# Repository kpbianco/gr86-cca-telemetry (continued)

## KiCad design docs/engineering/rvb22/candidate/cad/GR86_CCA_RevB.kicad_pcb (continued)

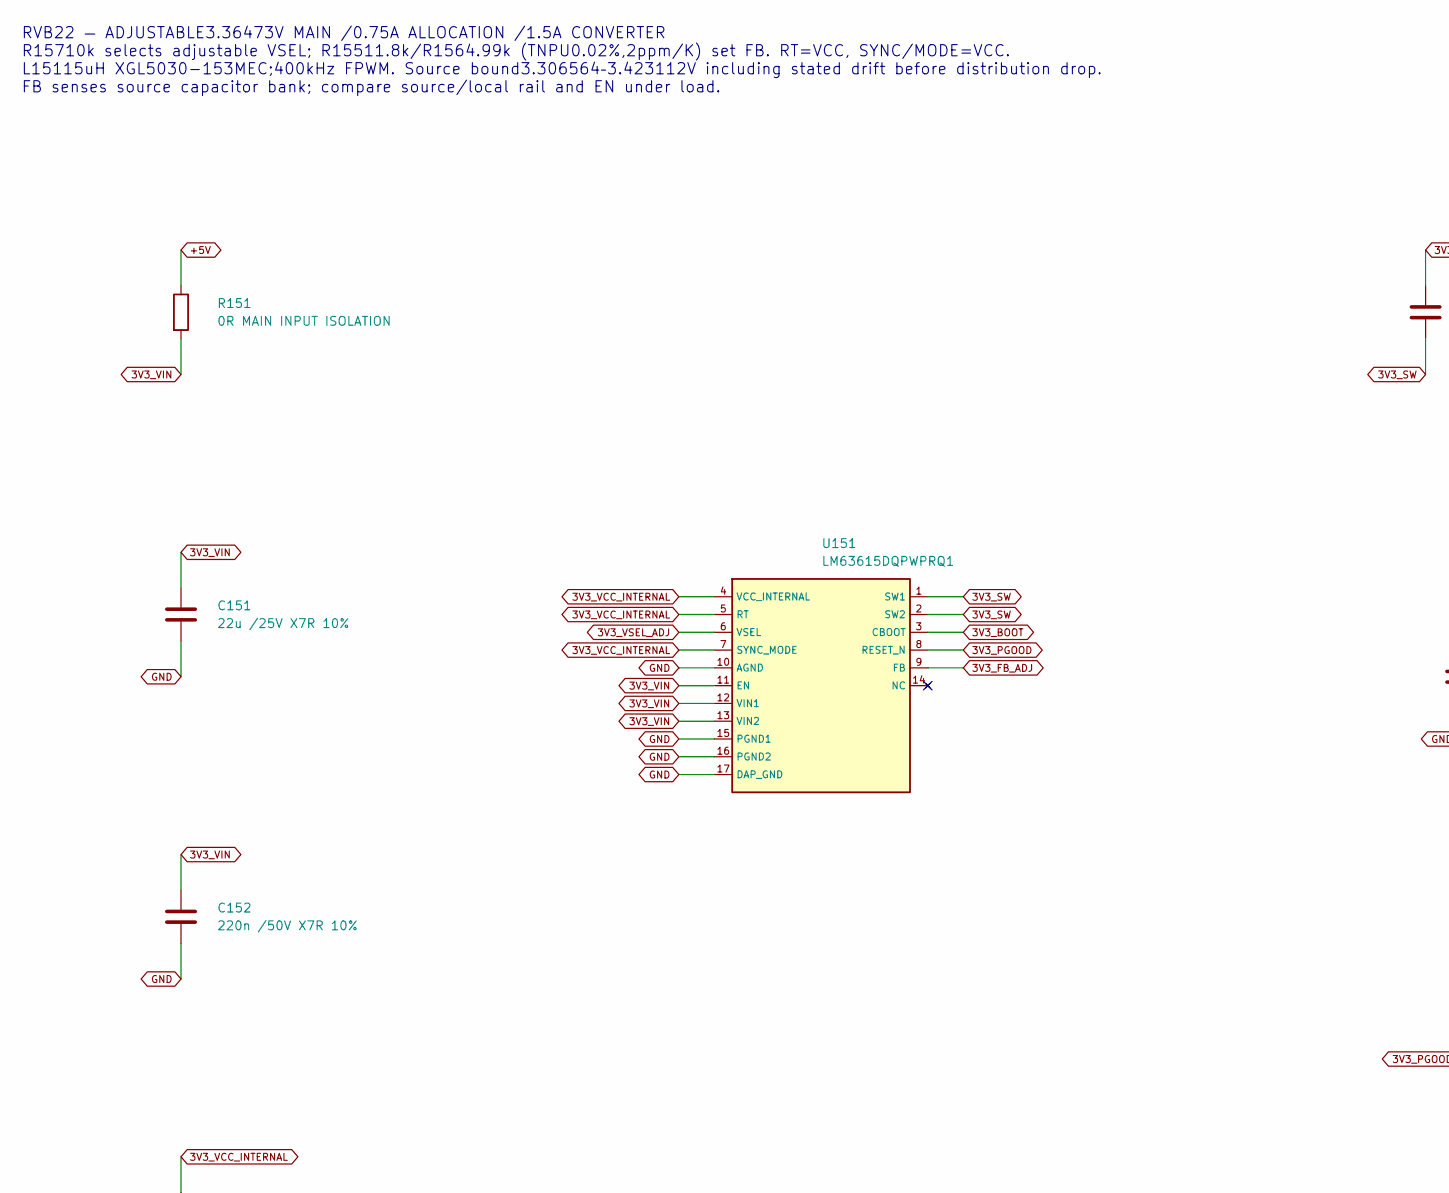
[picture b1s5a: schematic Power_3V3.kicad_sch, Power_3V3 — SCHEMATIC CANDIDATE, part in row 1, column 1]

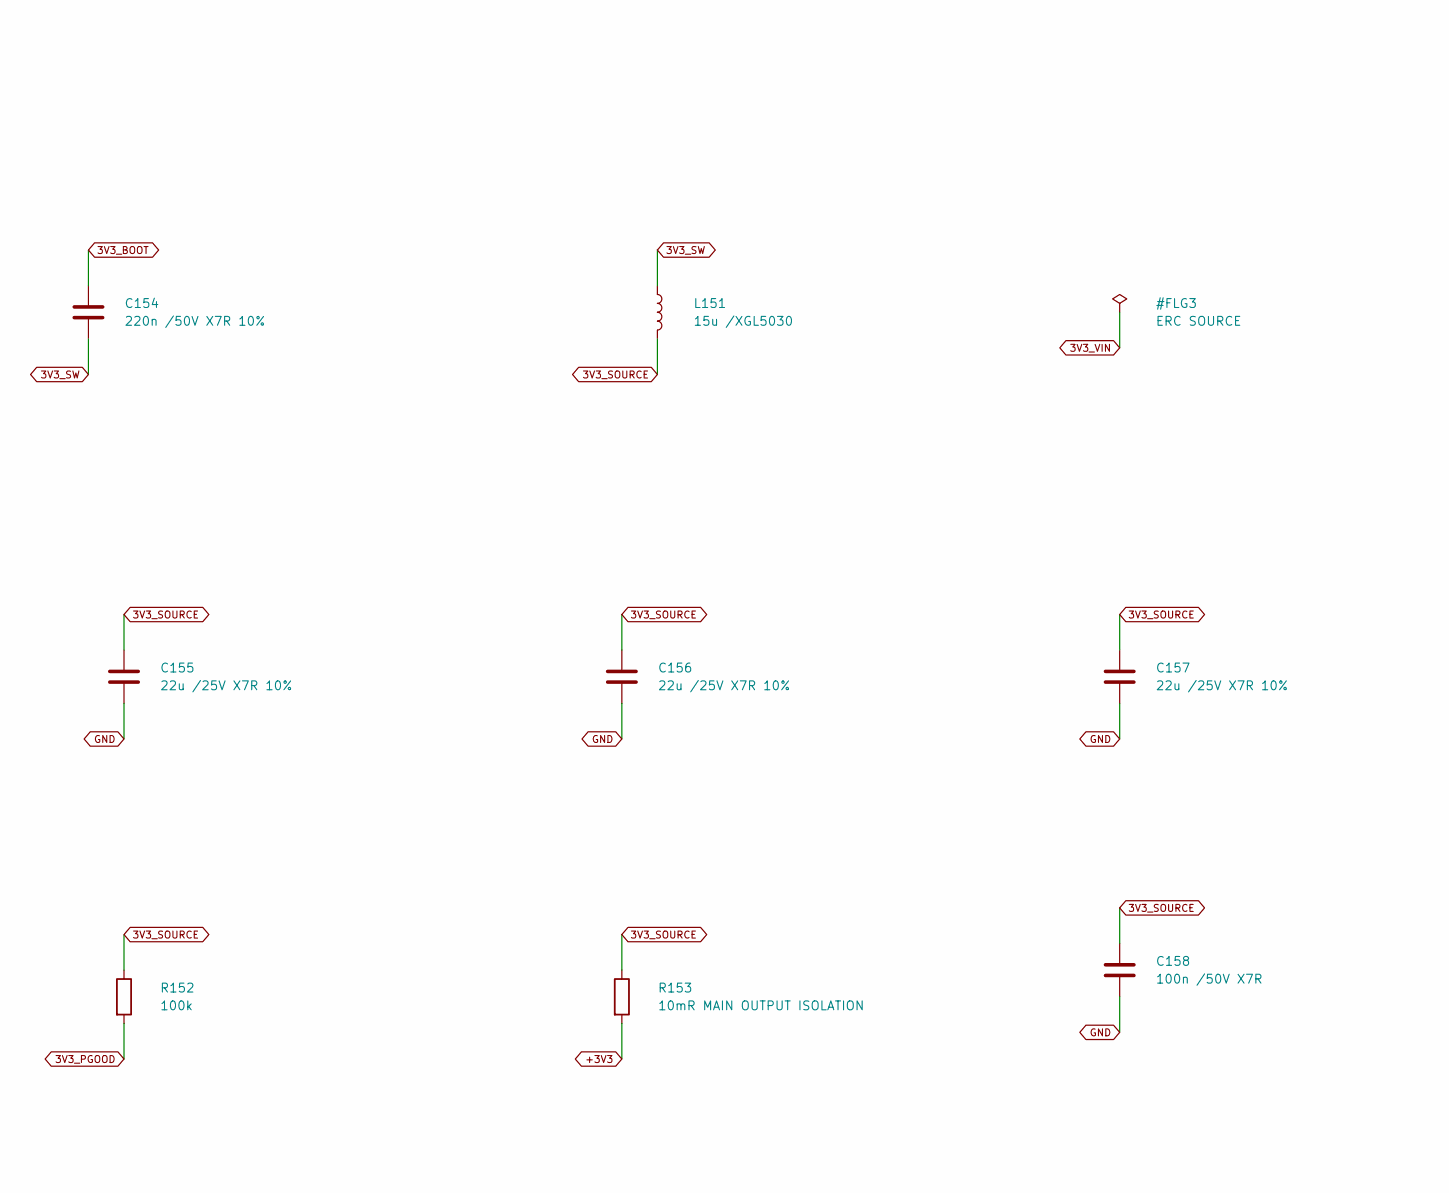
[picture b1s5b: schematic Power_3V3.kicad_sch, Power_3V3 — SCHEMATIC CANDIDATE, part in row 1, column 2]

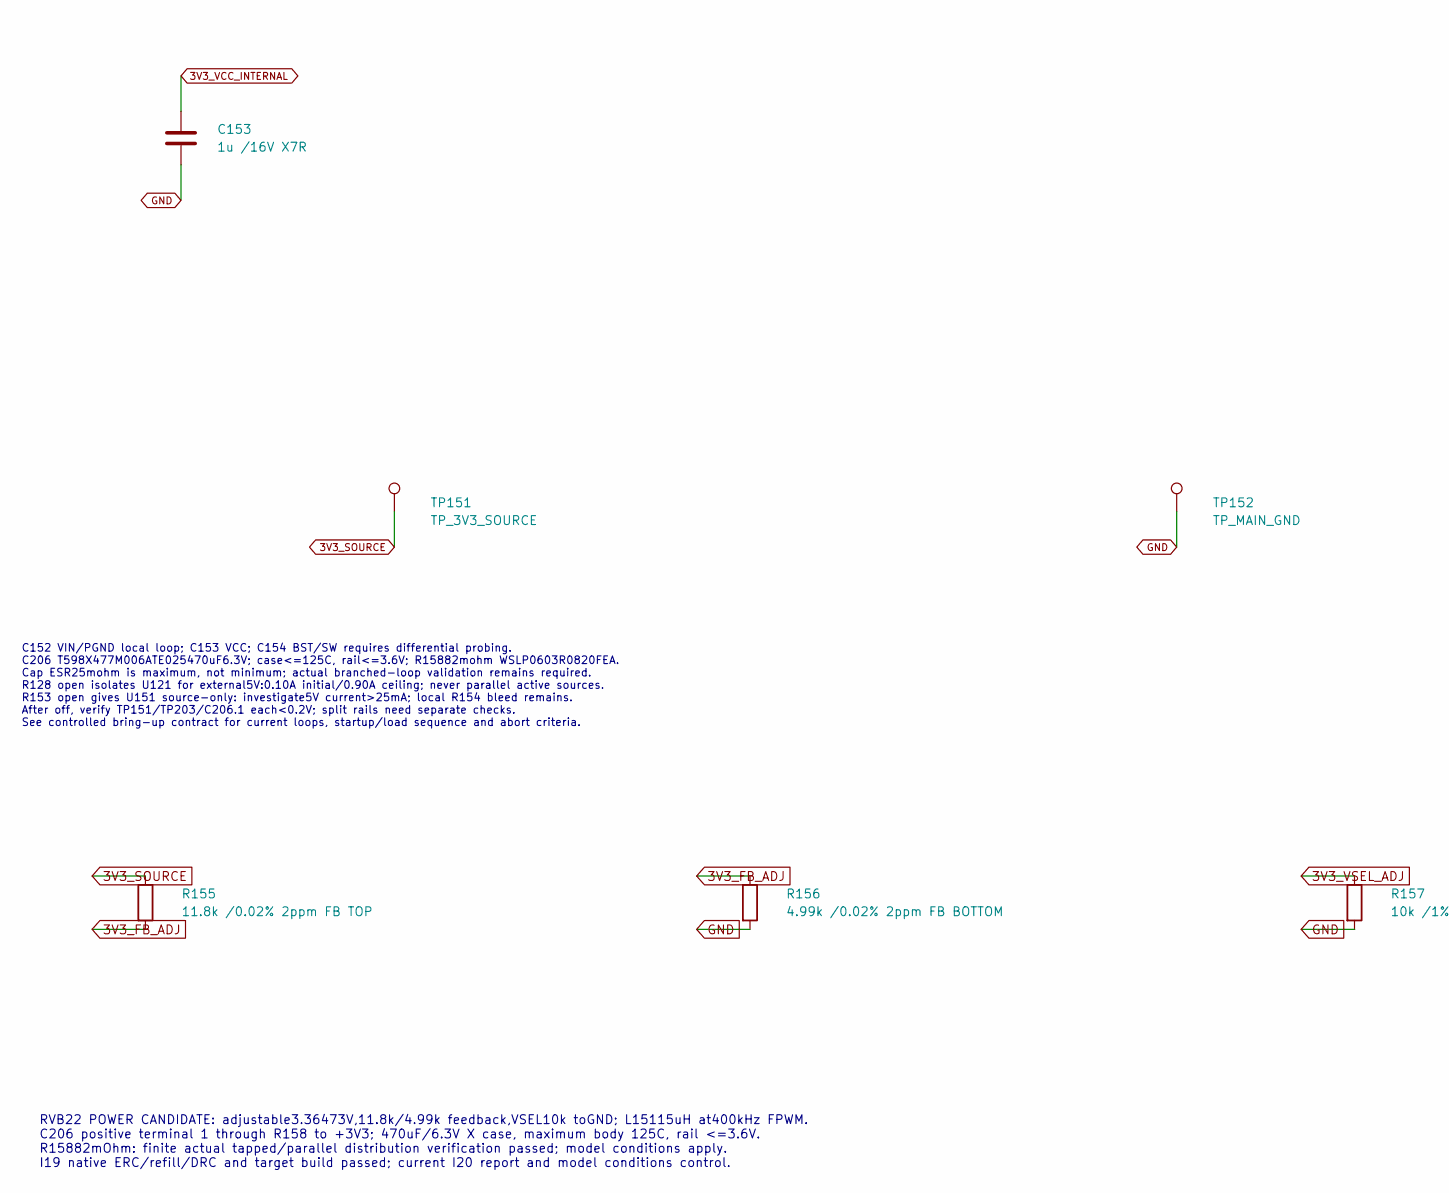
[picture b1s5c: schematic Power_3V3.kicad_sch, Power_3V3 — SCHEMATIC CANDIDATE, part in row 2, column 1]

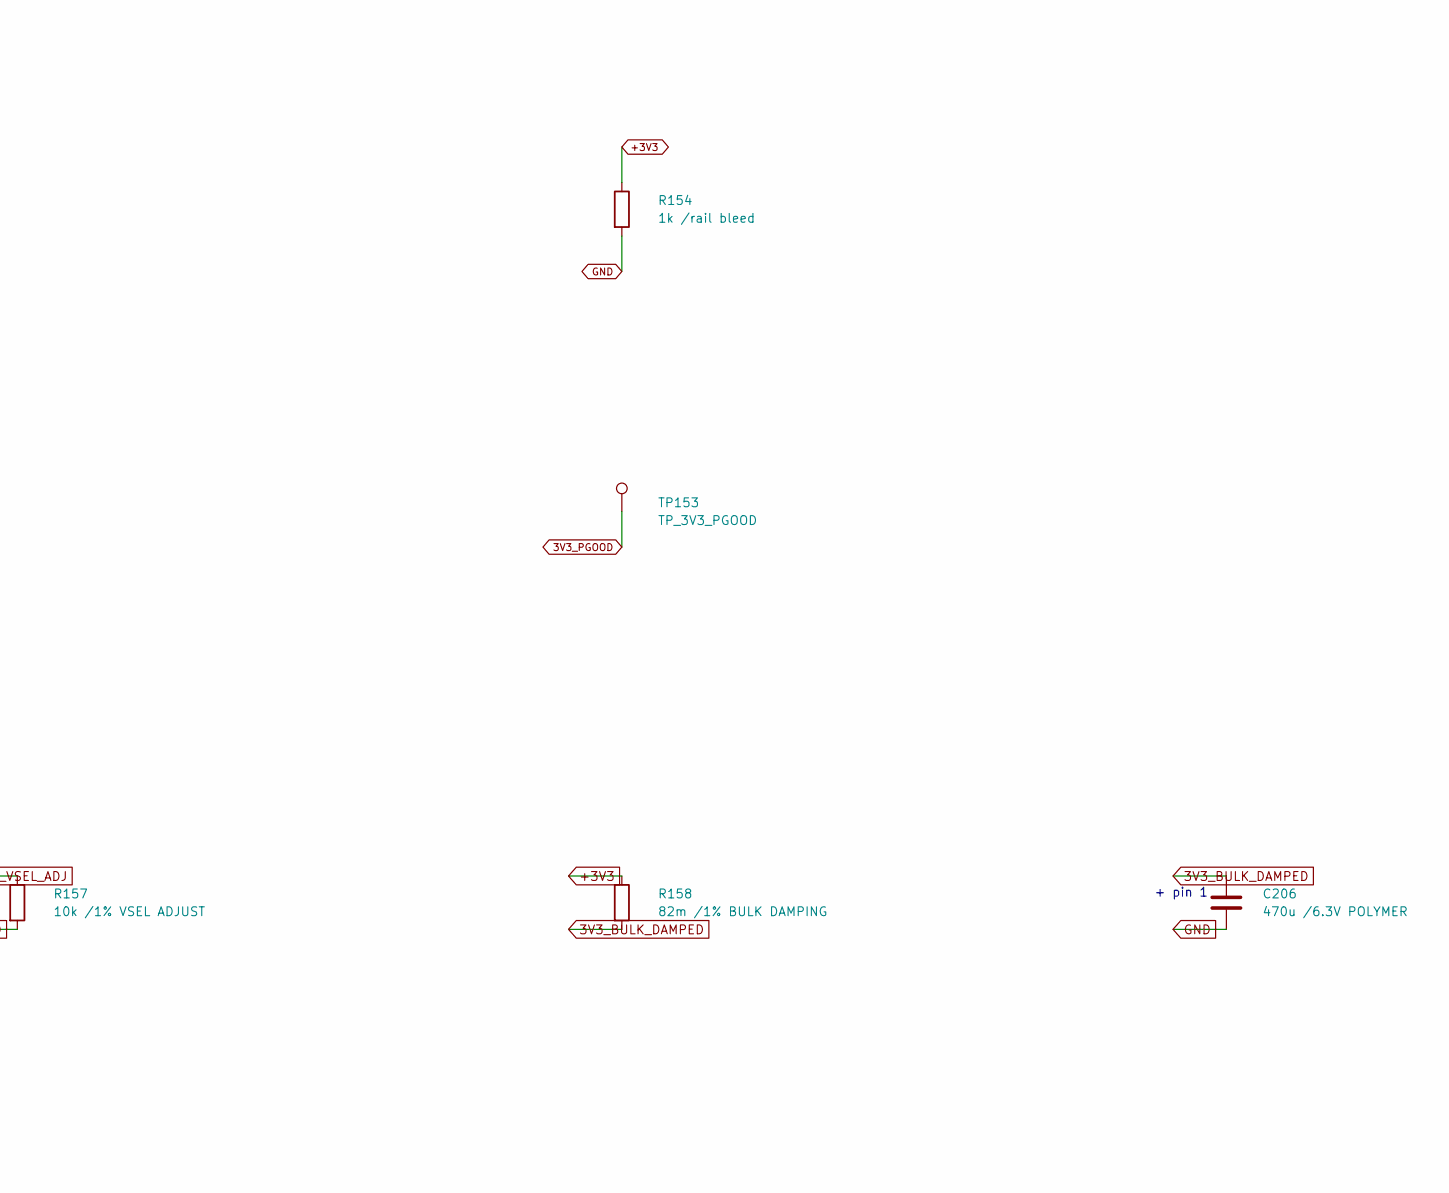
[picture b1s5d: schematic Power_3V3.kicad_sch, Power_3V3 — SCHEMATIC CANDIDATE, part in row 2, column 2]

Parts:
C151, C155, C156, C157: 22u /25V X7R 10%; C_1210_3225Metric; MPN MCAST32MSB7226KPNA01; LCSC C5372271
C152: 220n /50V X7R 10%; C_0603_1608Metric; MPN CGA3E3X7R1H224K080AB; LCSC C342967
C153: 1u /16V X7R; C_0603_1608Metric; MPN GCM188R71C105KA64D; LCSC C161212
C154: 220n /50V X7R 10%; C_0603_1608Metric_RVB22_C154; MPN CGA3E3X7R1H224K080AB; LCSC C342967
C158: 100n /50V X7R; C_0603_1608Metric; MPN GCM188R71H104KA57D; LCSC C85864
C206: 470u /6.3V POLYMER; KEMET_T598_X_7343_Median_RVB22_C206; MPN T598X477M006ATE025
L151: 15u /XGL5030; L_Coilcraft_XAL5030-XXX; MPN XGL5030-153MEC
R151: 0R MAIN INPUT ISOLATION; R_1206_3216Metric; MPN CRCW12060000Z0EA; LCSC C190124
R152: 100k; R_0603_1608Metric; MPN CRCW0603100KFKEA; LCSC C844916
R153: 10mR MAIN OUTPUT ISOLATION; WSLP0603_MANUFACTURER_R153; MPN WSLP0603R0100FEA
R154: 1k /rail bleed; R_0603_1608Metric; MPN CRCW06031K00FKEA; LCSC C844920
R155: 11.8k /0.02% 2ppm FB TOP; R_0603_1608Metric_RVB22_R155; MPN TNPU060311K8HWEA00
R156: 4.99k /0.02% 2ppm FB BOTTOM; R_0603_1608Metric_RVB22_R156; MPN TNPU06034K99HWEA00
R157: 10k /1% VSEL ADJUST; R_0603_1608Metric_RVB22_R157; MPN CRCW060310K0FKEA
R158: 82m /1% BULK DAMPING; WSLP0603_MANUFACTURER; MPN WSLP0603R0820FEA
TP151: TP_3V3_SOURCE; TestPoint_Pad_D1.5mm; MPN BARE PCB PAD
TP152: TP_MAIN_GND; TestPoint_Pad_D1.5mm; MPN BARE PCB PAD
TP153: TP_3V3_PGOOD; TestPoint_Pad_D1.5mm; MPN BARE PCB PAD
U151: LM63615DQPWPRQ1; HTSSOP-16-1EP_4.4x5mm_P0.65mm_EP3.4x5mm_Mask2.46x2.31mm_RVB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; MPN LM63615DQPWPRQ1; LCSC C2867799

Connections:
3V3_BOOT: C154.1, U151.3 (CBOOT)
3V3_BULK_DAMPED: C206.1, R158.2
3V3_FB_ADJ: R155.2, R156.1, U151.9 (FB)
3V3_PGOOD: R152.2, TP153.1, U151.8 (RESET_N)
3V3_SOURCE: C155.1, C156.1, C157.1, C158.1, L151.2, R152.1, R153.1, R155.1, TP151.1
3V3_SW: C154.2, L151.1, U151.1 (SW1), U151.2 (SW2)
3V3_VCC_INTERNAL: C153.1, U151.4 (VCC_INTERNAL), U151.5 (RT), U151.7 (SYNC_MODE)
3V3_VIN: C151.1, C152.1, R151.2, U151.11 (EN), U151.12 (VIN1), U151.13 (VIN2)
3V3_VSEL_ADJ: R157.1, U151.6 (VSEL)
+3V3: R153.2, R154.1, R158.1; also elsewhere on the board
+5V: R151.1; also elsewhere on the board
GND: C151.2, C152.2, C153.2, C155.2, C156.2, C157.2, C158.2, C206.2, R154.2, R156.2, R157.2, TP152.1, U151.10 (AGND), U151.15 (PGND1), U151.16 (PGND2), U151.17 (DAP_GND); also elsewhere on the board

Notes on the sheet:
RVB22 — ADJUSTABLE3.36473V MAIN /0.75A ALLOCATION /1.5A CONVERTER R15710k selects adjustable VSEL; R15511.8k/R1564.99k (TNPU0.02%,2ppm/K) set FB. RT=VCC, SYNC/MODE=VCC. L15115uH XGL5030-153MEC;400kHz FPWM. Source bound3.306564–3.423112V including stated drift before distribution drop. FB senses sou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
C152 VIN/PGND local loop; C153 VCC; C154 BST/SW requires differential probing. C206 T598X477M006ATE025470uF6.3V; case<=125C, rail<=3.6V; R15882mohm WSLP0603R0820FEA. Cap ESR25mohm is maximum, not minimum; actual branched-loop validation remains required. R128 open isolates U121 for external5V:0.10A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
+ pin 1
RVB22 POWER CANDIDATE: adjustable3.36473V,11.8k/4.99k feedback,VSEL10k toGND; L15115uH at400kHz FPWM. C206 positive terminal 1 through R158 to +3V3; 470uF/6.3V X case, maximum body 125C, rail <=3.6V. R15882mOhm: finite actual tapped/parallel distribution verification passed; model conditions apply.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

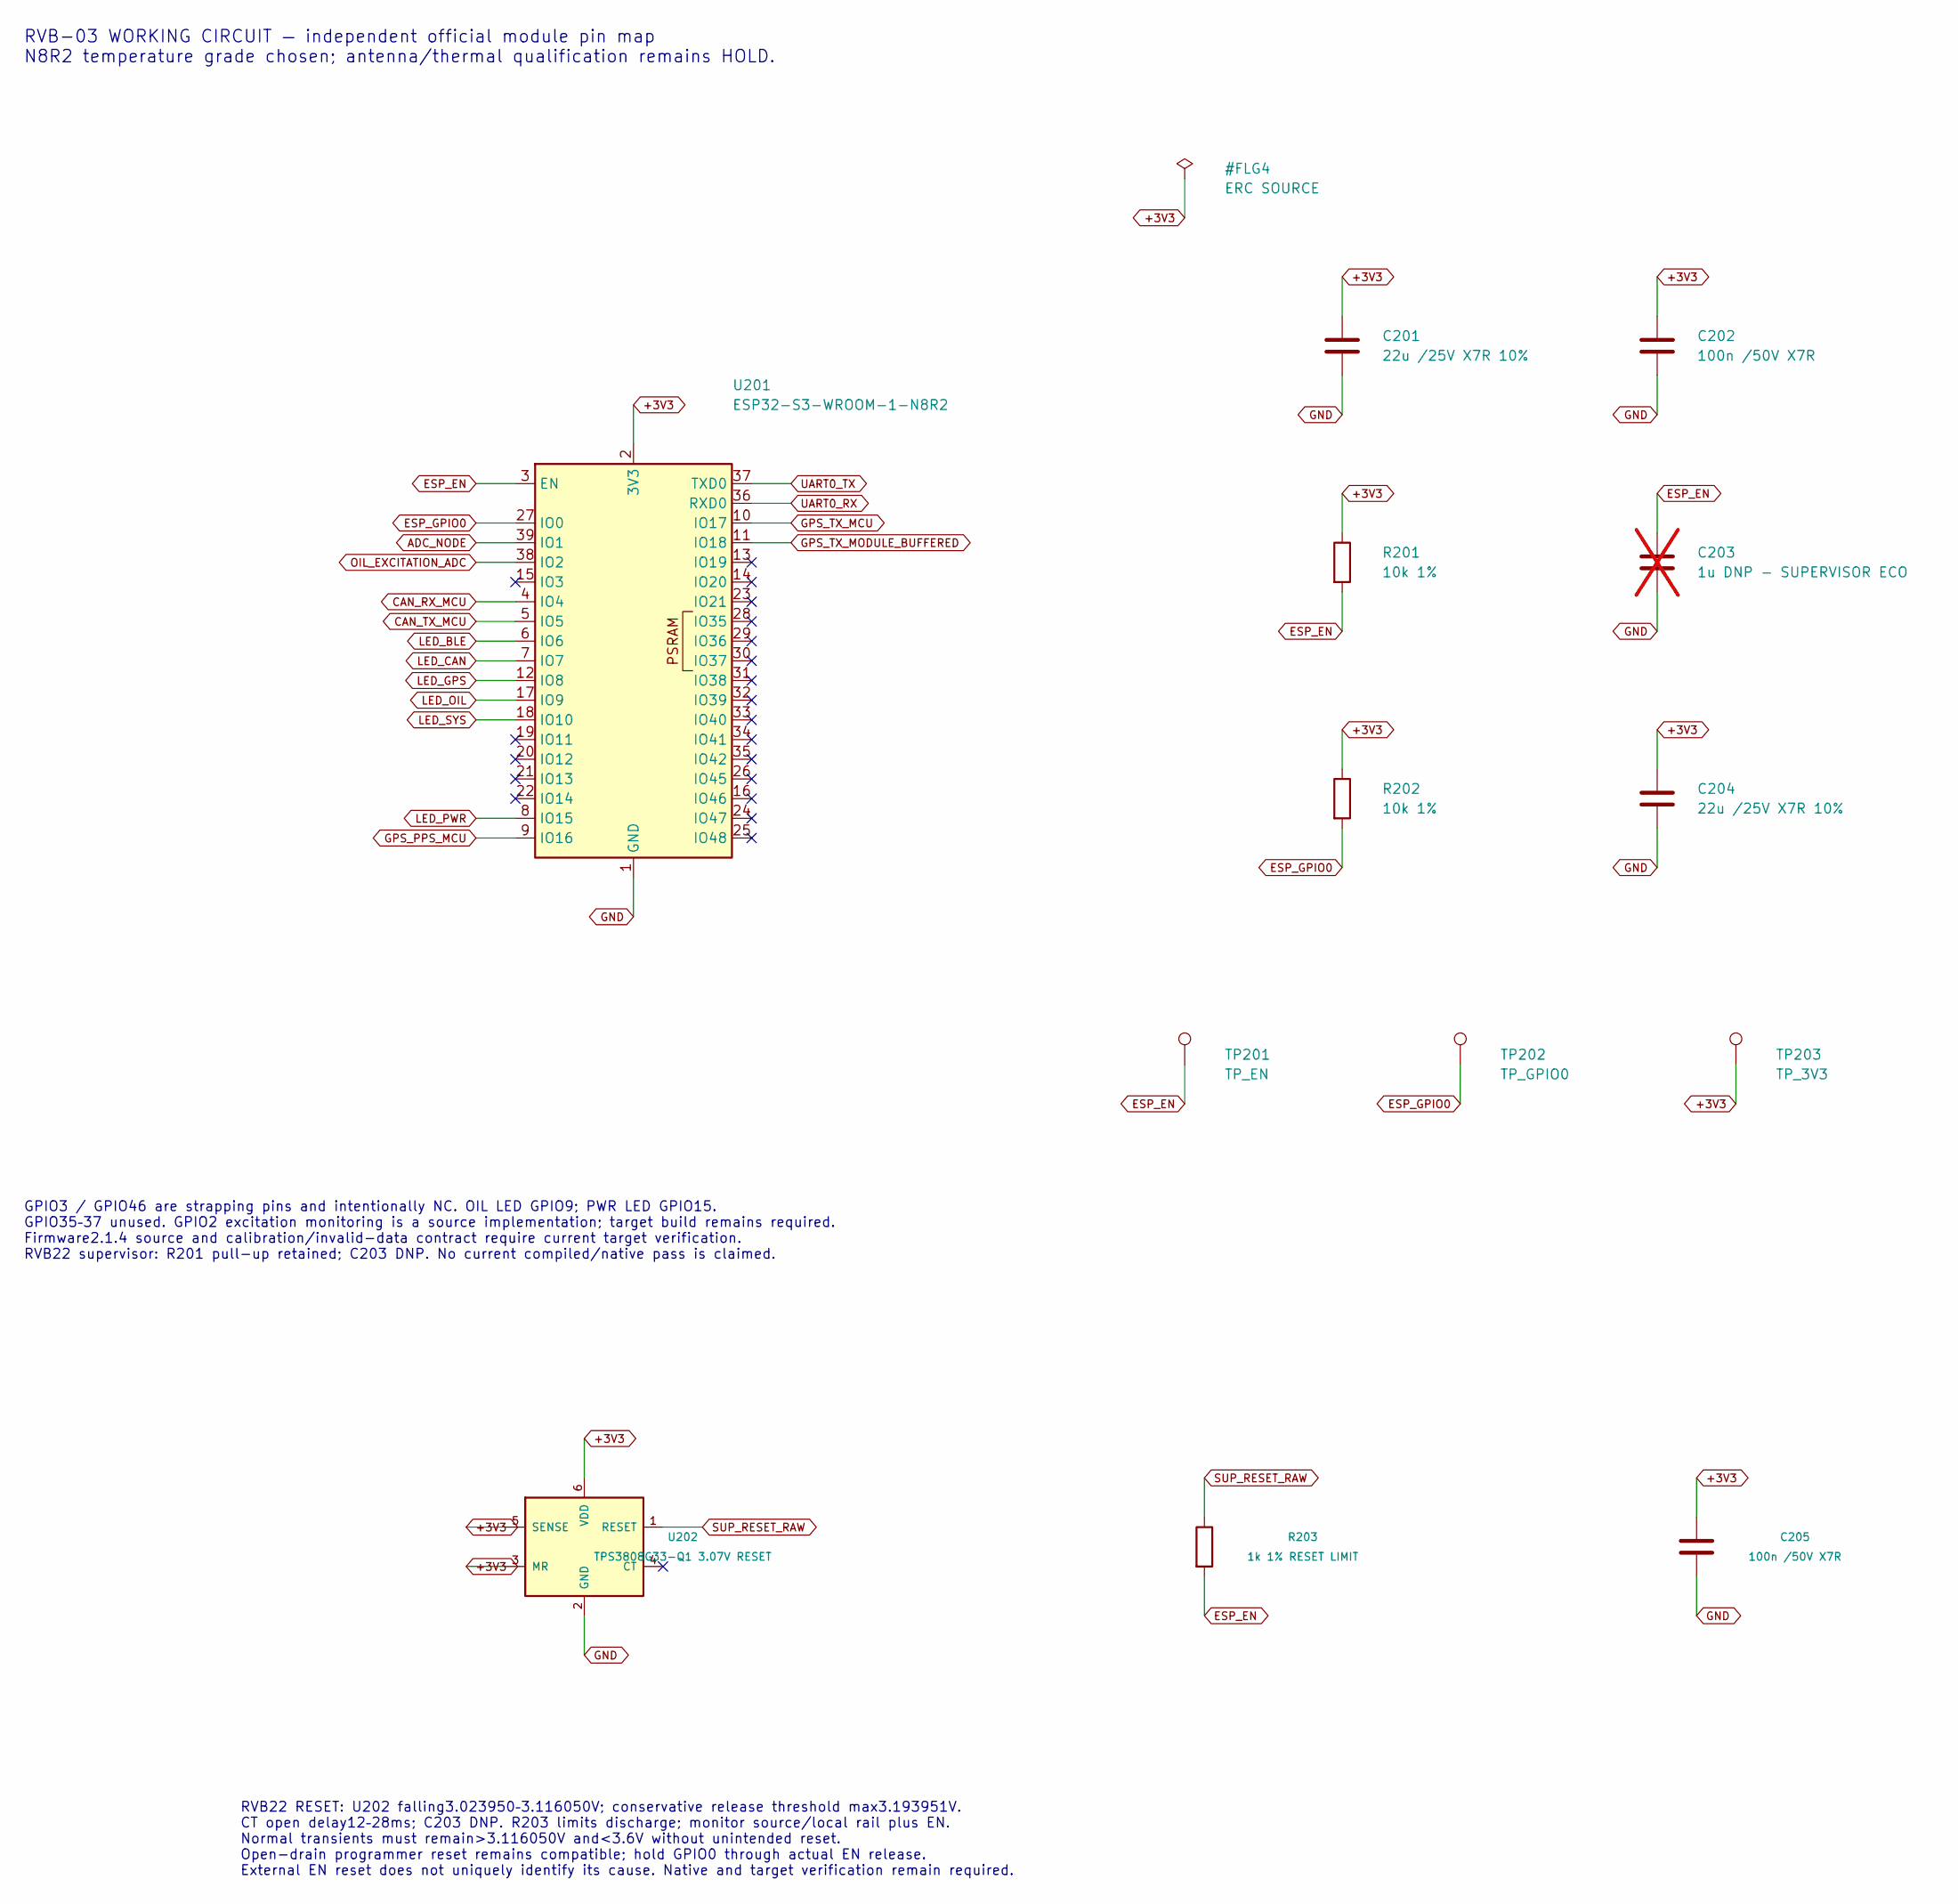
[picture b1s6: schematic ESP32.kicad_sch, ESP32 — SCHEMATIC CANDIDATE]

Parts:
C201, C204: 22u /25V X7R 10%; C_1210_3225Metric; MPN MCAST32MSB7226KPNA01; LCSC C5372271
C202: 100n /50V X7R; C_0603_1608Metric; MPN GCM188R71H104KA57D; LCSC C85864
C203: 1u DNP - SUPERVISOR ECO; C_0603_1608Metric; MPN GCM188R71C105KA64D; LCSC C161212; not fitted
C205: 100n /50V X7R; C_0603_1608Metric_RVB22_C205; MPN GCM188R71H104KA57D; LCSC C85864
R201, R202: 10k 1%; R_0603_1608Metric; MPN CRCW060310K0FKEA; LCSC C844918
R203: 1k 1% RESET LIMIT; R_0603_1608Metric_RVB22_R203; MPN CRCW06031K00FKEA; LCSC C844920
TP201: TP_EN; TestPoint_Pad_D1.5mm; MPN BARE PCB PAD
TP202: TP_GPIO0; TestPoint_Pad_D1.5mm; MPN BARE PCB PAD
TP203: TP_3V3; TestPoint_Pad_D1.5mm; MPN BARE PCB PAD
U201: ESP32-S3-WROOM-1-N8R2; ESP32-S3-WROOM-1_RVB22_U201_TH48; MPN ESP32-S3-WROOM-1-N8R2; LCSC C2913204
U202: TPS3808G33-Q1 3.07V RESET; TPS3808_DBV0006A; MPN TPS3808G33QDBVRQ1

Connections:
+3V3: C201.1, C202.1, C204.1, C205.1, R201.1, R202.1, TP203.1, U201.2 (3V3), U202.3 (MR), U202.5 (SENSE), U202.6 (VDD); also elsewhere on the board
ADC_NODE: U201.39 (IO1); also elsewhere on the board
CAN_RX_MCU: U201.4 (IO4); also elsewhere on the board
CAN_TX_MCU: U201.5 (IO5); also elsewhere on the board
ESP_EN: C203.1, R201.2, R203.2, TP201.1, U201.3 (EN); also elsewhere on the board
ESP_GPIO0: R202.2, TP202.1, U201.27 (IO0); also elsewhere on the board
GND: C201.2, C202.2, C203.2, C204.2, C205.2, U201.1 (GND), U201.40 (GND), U201.41 (GND), U202.2 (GND); also elsewhere on the board
GPS_PPS_MCU: U201.9 (IO16); also elsewhere on the board
GPS_TX_MCU: U201.10 (IO17); also elsewhere on the board
GPS_TX_MODULE_BUFFERED: U201.11 (IO18); also elsewhere on the board
LED_BLE: U201.6 (IO6); also elsewhere on the board
LED_CAN: U201.7 (IO7); also elsewhere on the board
LED_GPS: U201.12 (IO8); also elsewhere on the board
LED_OIL: U201.17 (IO9); also elsewhere on the board
LED_PWR: U201.8 (IO15); also elsewhere on the board
LED_SYS: U201.18 (IO10); also elsewhere on the board
OIL_EXCITATION_ADC: U201.38 (IO2); also elsewhere on the board
SUP_RESET_RAW: R203.1, U202.1 (RESET)
UART0_RX: U201.36 (RXD0); also elsewhere on the board
UART0_TX: U201.37 (TXD0); also elsewhere on the board

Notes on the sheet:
RVB-03 WORKING CIRCUIT — independent official module pin map N8R2 temperature grade chosen; antenna/thermal qualification remains HOLD.
GPIO3 / GPIO46 are strapping pins and intentionally NC. OIL LED GPIO9; PWR LED GPIO15. GPIO35–37 unused. GPIO2 excitation monitoring is a source implementation; target build remains required. Firmware2.1.4 source and calibration/invalid-data contract require current target verification. RVB22 super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
RVB22 RESET: U202 falling3.023950–3.116050V; conservative release threshold max3.193951V. CT open delay12–28ms; C203 DNP. R203 limits discharge; monitor source/local rail plus EN. Normal transients must remain>3.116050V and<3.6V without unintended reset. Open-drain programmer reset remains compatib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

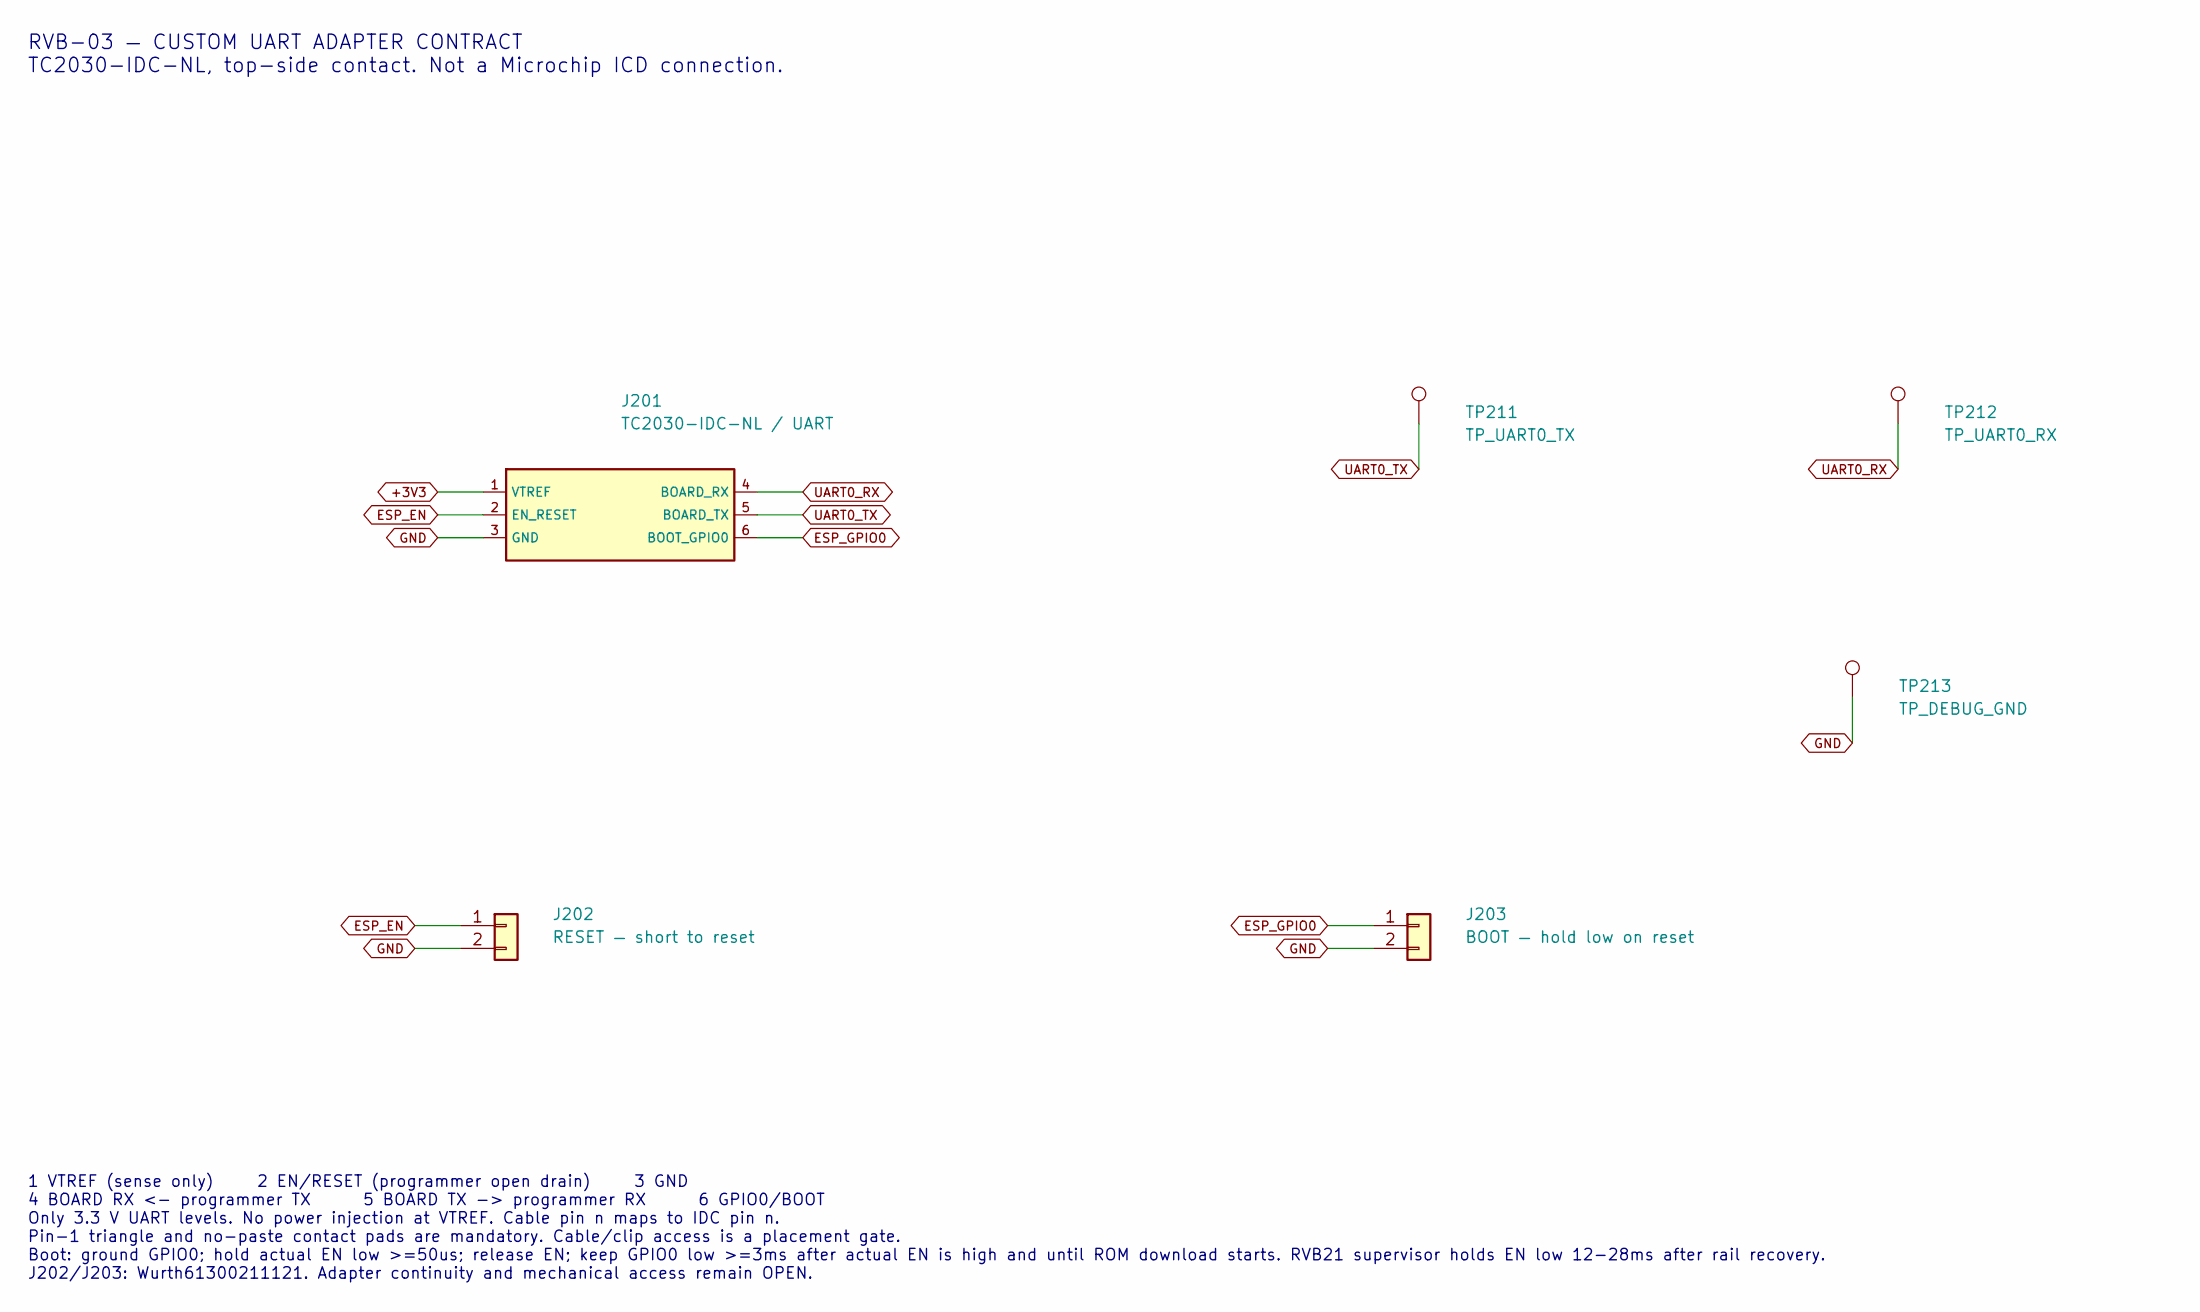
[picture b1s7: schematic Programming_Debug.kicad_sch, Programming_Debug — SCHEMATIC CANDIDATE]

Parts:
J201: TC2030-IDC-NL / UART; Tag-Connect_TC2030-IDC-NL_2x03_P1.27mm_Vertical; MPN TC2030-IDC-NL (tool, not assembled comp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
J202: RESET — short to reset; Wurth_61300211121_1x02; MPN 61300211121; LCSC C2915055
J203: BOOT — hold low on reset; Wurth_61300211121_1x02; MPN 61300211121; LCSC C2915055
TP211: TP_UART0_TX; TestPoint_Pad_D1.5mm; MPN BARE PCB PAD
TP212: TP_UART0_RX; TestPoint_Pad_D1.5mm; MPN BARE PCB PAD
TP213: TP_DEBUG_GND; TestPoint_Pad_D1.5mm; MPN BARE PCB PAD

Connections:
+3V3: J201.1 (VTREF); also elsewhere on the board
ESP_EN: J201.2 (EN_RESET), J202.1; also elsewhere on the board
ESP_GPIO0: J201.6 (BOOT_GPIO0), J203.1; also elsewhere on the board
GND: J201.3 (GND), J202.2, J203.2, TP213.1; also elsewhere on the board
UART0_RX: J201.4 (BOARD_RX), TP212.1; also elsewhere on the board
UART0_TX: J201.5 (BOARD_TX), TP211.1; also elsewhere on the board

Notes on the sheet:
RVB-03 — CUSTOM UART ADAPTER CONTRACT TC2030-IDC-NL, top-side contact. Not a Microchip ICD connection.
1 VTREF (sense only) 2 EN/RESET (programmer open drain) 3 GND 4 BOARD RX <- programmer TX 5 BOARD TX -> programmer RX 6 GPIO0/BOOT Only 3.3 V UART levels. No power injection at VTREF. Cable pin n maps to IDC pin n. Pin-1 triangle and no-paste contact pads are mandatory. Cable/clip access is a place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

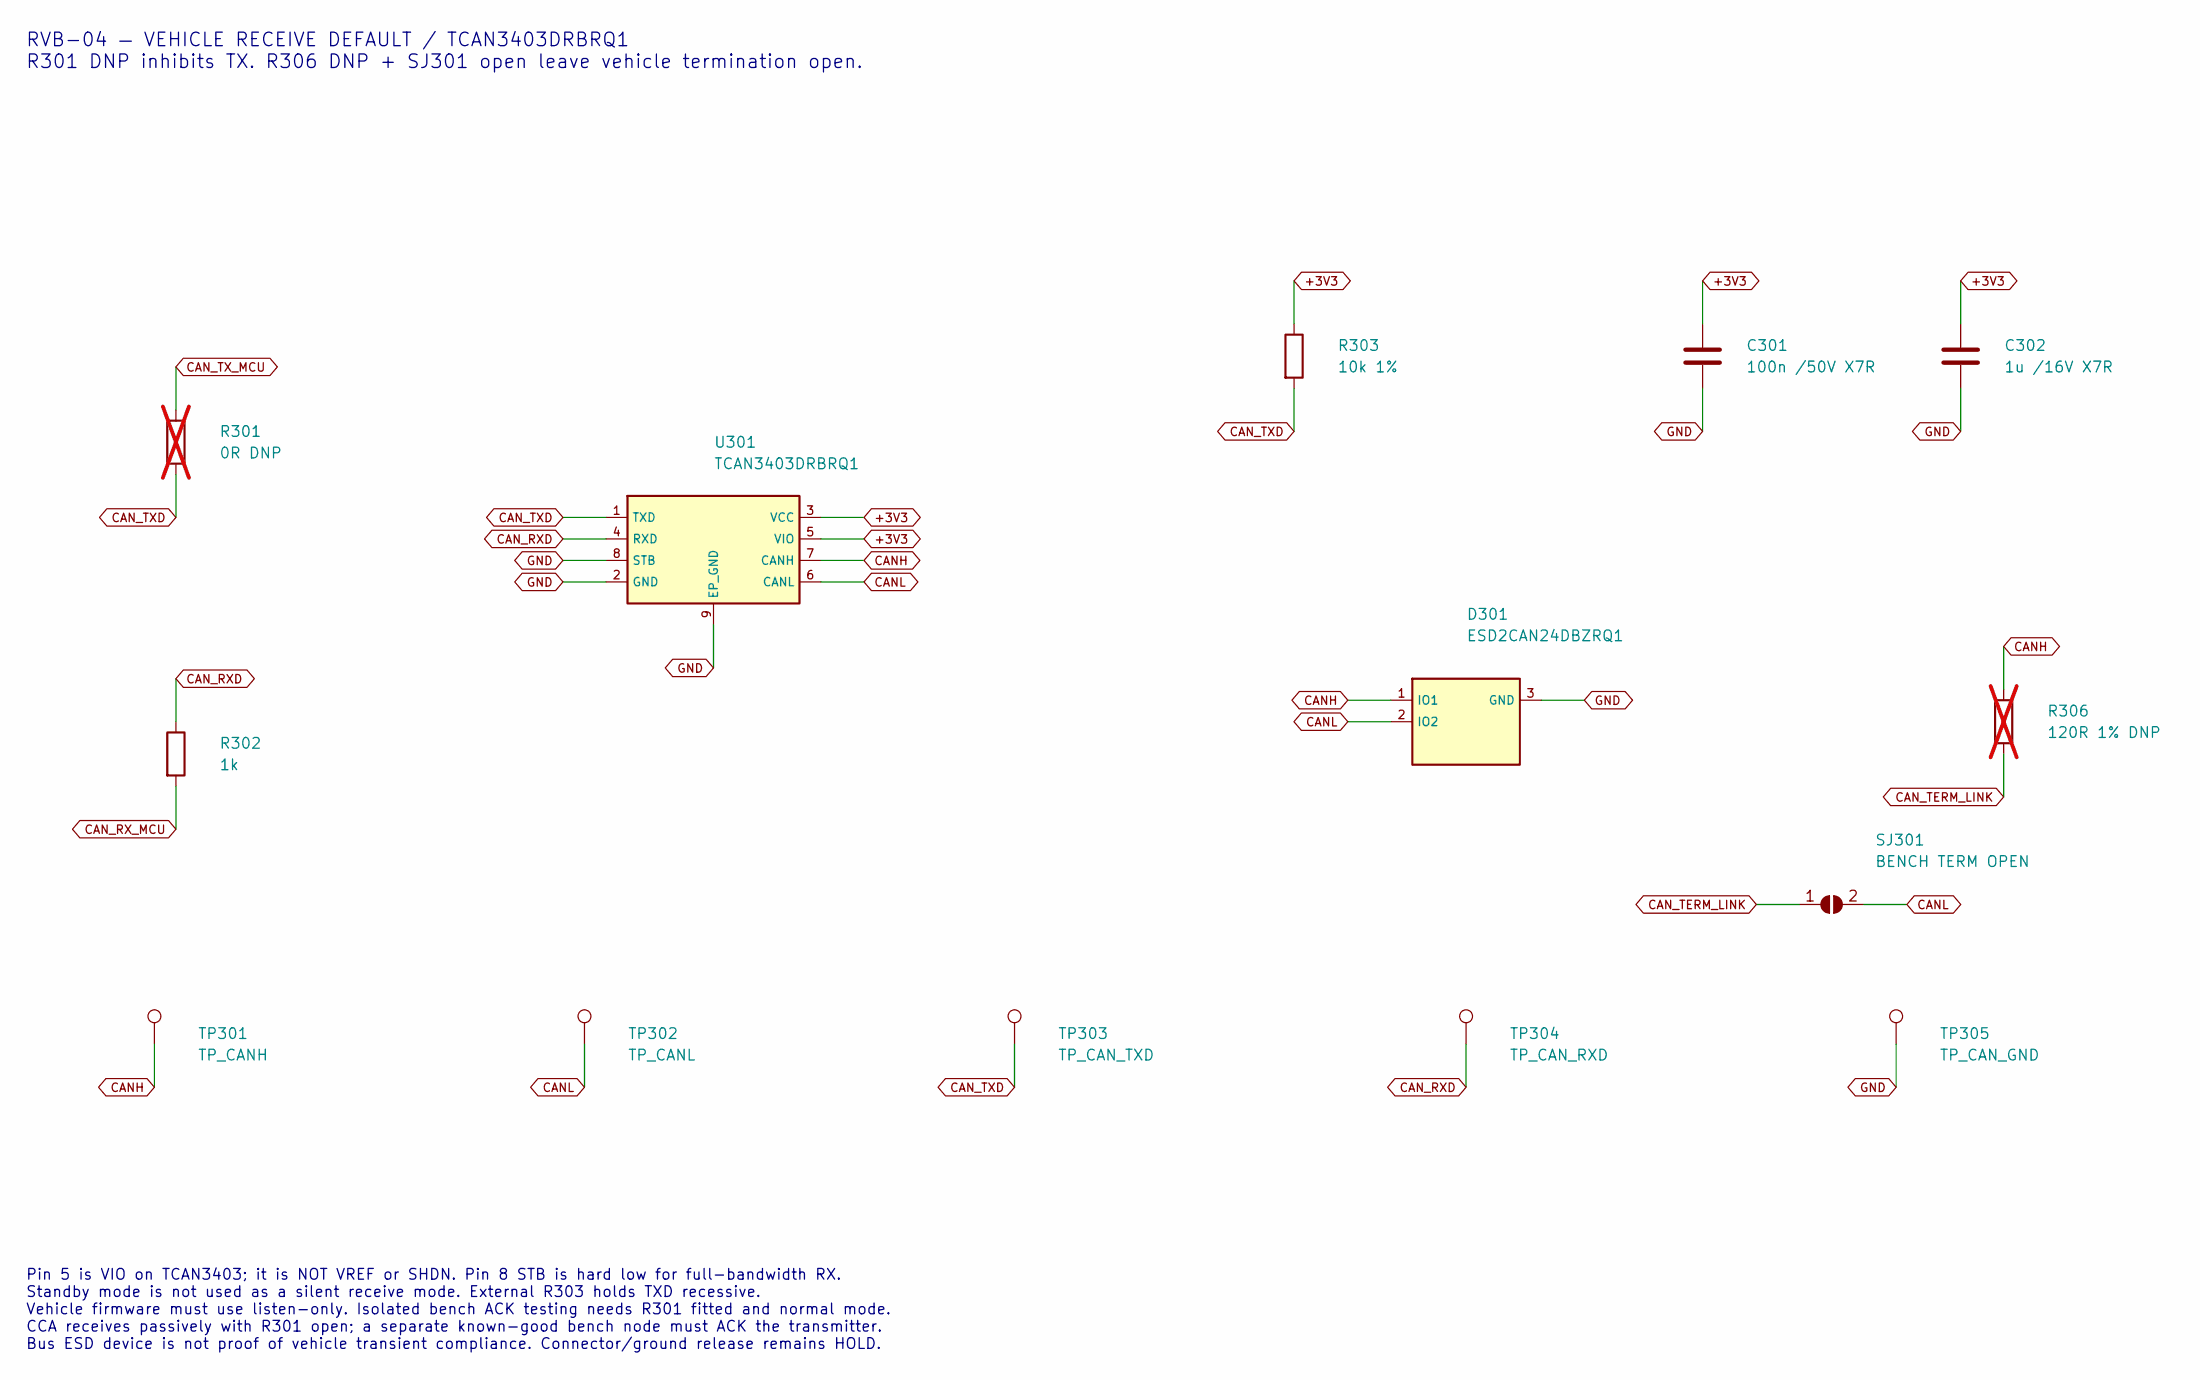
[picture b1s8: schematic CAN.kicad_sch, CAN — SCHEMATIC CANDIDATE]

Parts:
C301: 100n /50V X7R; C_0603_1608Metric; MPN GCM188R71H104KA57D; LCSC C85864
C302: 1u /16V X7R; C_0603_1608Metric; MPN GCM188R71C105KA64D; LCSC C161212
D301: ESD2CAN24DBZRQ1; SOT-23; MPN ESD2CAN24DBZRQ1; LCSC C5736151
R301: 0R DNP; R_0603_1608Metric; MPN CRCW06030000Z0EA; not fitted
R302: 1k; R_0603_1608Metric; MPN CRCW06031K00FKEA; LCSC C844920
R303: 10k 1%; R_0603_1608Metric; MPN CRCW060310K0FKEA; LCSC C844918
R306: 120R 1% DNP; R_1206_3216Metric; MPN CRCW1206120RFKEA; not fitted
SJ301: BENCH TERM OPEN; SolderJumper-2_P1.3mm_Open_Pad1.0x1.5mm; MPN BARE PCB OPEN SOLDER LINK
TP301: TP_CANH; TestPoint_Pad_D1.5mm; MPN BARE PCB PAD
TP302: TP_CANL; TestPoint_Pad_D1.5mm; MPN BARE PCB PAD
TP303: TP_CAN_TXD; TestPoint_Pad_D1.5mm; MPN BARE PCB PAD
TP304: TP_CAN_RXD; TestPoint_Pad_D1.5mm; MPN BARE PCB PAD
TP305: TP_CAN_GND; TestPoint_Pad_D1.5mm; MPN BARE PCB PAD
U301: TCAN3403DRBRQ1; TI_DRB0008J_TCAN3403; MPN TCAN3403DRBRQ1; LCSC C32921356

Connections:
+3V3: C301.1, C302.1, R303.1, U301.3 (VCC), U301.5 (VIO); also elsewhere on the board
CANH: D301.1 (IO1), R306.1, TP301.1, U301.7 (CANH); also elsewhere on the board
CANL: D301.2 (IO2), SJ301.2 (B), TP302.1, U301.6 (CANL); also elsewhere on the board
CAN_RXD: R302.1, TP304.1, U301.4 (RXD)
CAN_RX_MCU: R302.2; also elsewhere on the board
CAN_TERM_LINK: R306.2, SJ301.1 (A)
CAN_TXD: R301.2, R303.2, TP303.1, U301.1 (TXD)
CAN_TX_MCU: R301.1; also elsewhere on the board
GND: C301.2, C302.2, D301.3 (GND), TP305.1, U301.2 (GND), U301.8 (STB), U301.9 (EP_GND); also elsewhere on the board

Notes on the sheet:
RVB-04 — VEHICLE RECEIVE DEFAULT / TCAN3403DRBRQ1 R301 DNP inhibits TX. R306 DNP + SJ301 open leave vehicle termination open.
Pin 5 is VIO on TCAN3403; it is NOT VREF or SHDN. Pin 8 STB is hard low for full-bandwidth RX. Standby mode is not used as a silent receive mode. External R303 holds TXD recessive. Vehicle firmware must use listen-only. Isolated bench ACK testing needs R301 fitted and normal mode. CCA receives pass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
